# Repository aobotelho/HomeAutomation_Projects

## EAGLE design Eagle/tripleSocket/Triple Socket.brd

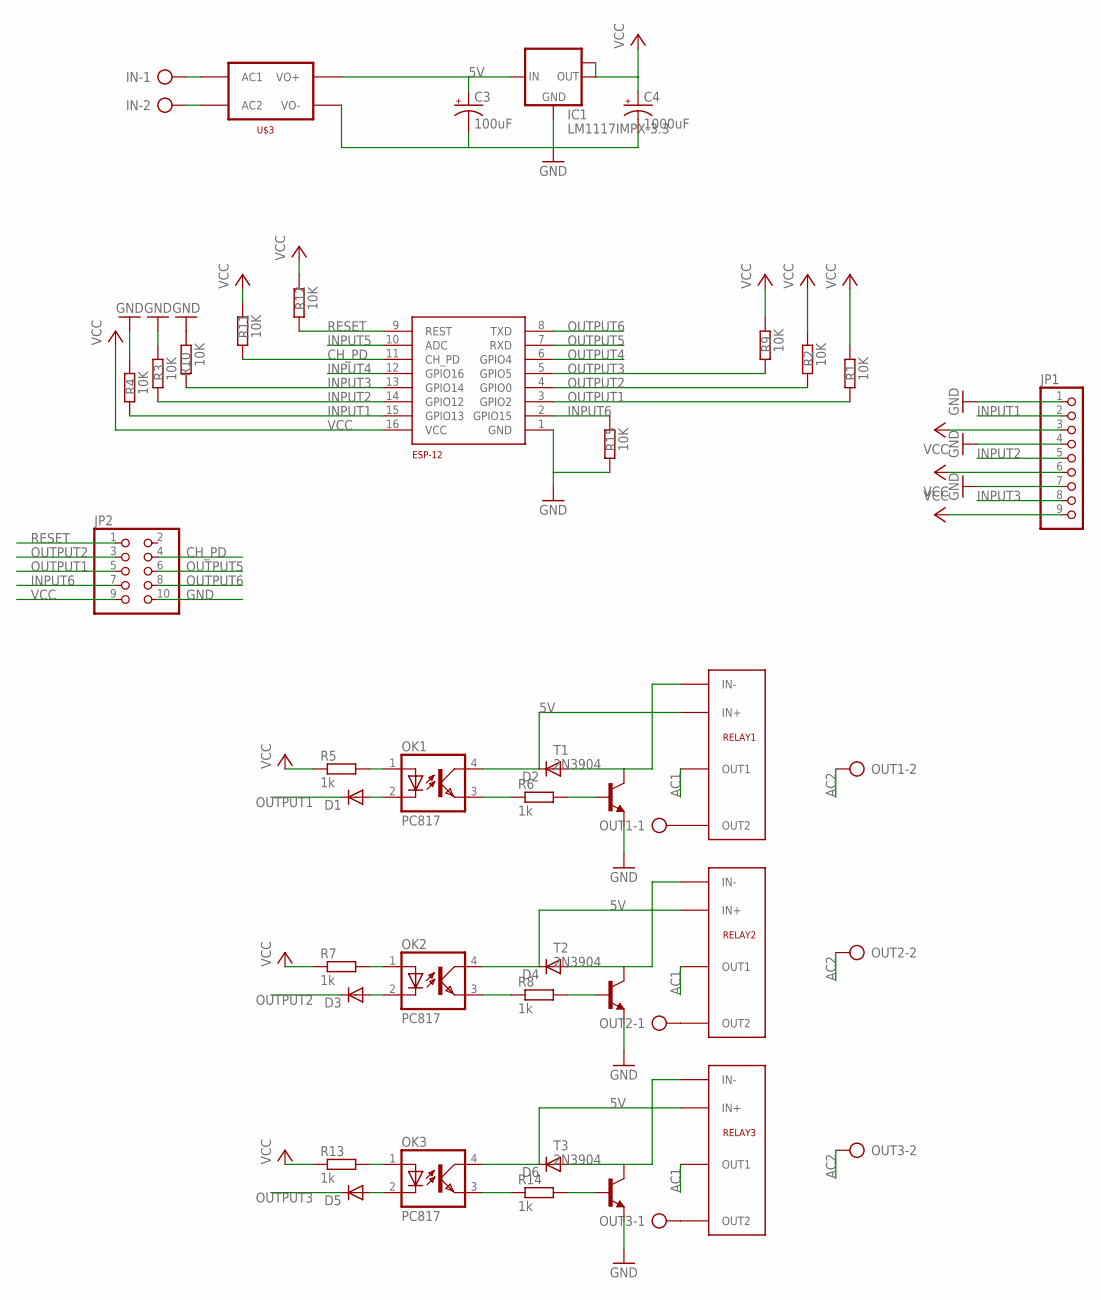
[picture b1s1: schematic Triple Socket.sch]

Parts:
C3: 100uF; E5-10,5
C4: 1000uF; E5-10,5
D1, D2, D3, D4, D5, D6: DIODE-SOD80C; SOD80C
ESP-12: ESP8266_ESP-12; ESP8266-ESP12
IC1: LM1117IMPX-3.3; SOT223
IN: AK500/2-H
JP1: PINHD-1X9; 1X09
JP2: PINHD-2X5; 2X05
OK1, OK2, OK3: PC817; DIL04
OUT1, OUT2, OUT3: AK500/2-H
R1, R2, R3, R4, R9, R10, R11, R12, R15: 10K; R0805
R5, R6, R7, R8, R13, R14: 1k; R0805
RELAY1, RELAY2, RELAY3: G3MB-202P
T1, T2, T3: 2N3904; TO92
U$3: HLK-PM01

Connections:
5V: C3.+, D2.C, D4.C, D6.C, IC1.3 (IN), OK1.4 (COL), OK2.4 (COL), OK3.4 (COL), RELAY1.IN+, RELAY2.IN+, RELAY3.IN+, U$3.VO+
AC1: IN.1, RELAY1.OUT1, RELAY2.OUT1, RELAY3.OUT1, U$3.AC1
AC2: IN.2, OUT1.2, OUT2.2, OUT3.2, U$3.AC2
CH_PD: ESP-12.11 (CH_PD), JP2.4, R11.1
GND: C3.-, C4.-, ESP-12.1 (GND), IC1.1 (GND), JP1.1, JP1.4, JP1.7, JP2.10, R3.1, R4.2, R10.1, R15.1, T1.3 (E), T2.3 (E), T3.3 (E), U$3.VO-
INPUT1: ESP-12.15 (GPIO13), JP1.2, R4.1
INPUT2: ESP-12.14 (GPIO12), JP1.5, R3.2
INPUT3: ESP-12.13 (GPIO14), JP1.8, R10.2
INPUT4: ESP-12.12 (GPIO16)
INPUT5: ESP-12.10 (ADC)
INPUT6: ESP-12.2 (GPIO15), JP2.7, R15.2
unnamed: OUT2.1, RELAY2.OUT2
unnamed: R14.2, T3.2 (B)
unnamed: D6.A, RELAY3.IN-, T3.1 (C)
unnamed: OUT1.1, RELAY1.OUT2
unnamed: OUT3.1, RELAY3.OUT2
unnamed: R6.2, T1.2 (B)
unnamed: D2.A, RELAY1.IN-, T1.1 (C)
unnamed: R8.2, T2.2 (B)
unnamed: D4.A, RELAY2.IN-, T2.1 (C)
OPTO_EMITTER2: OK2.3 (EMIT), R8.1
OPTO_LED+1: OK1.1 (A), R5.2
OPTO_LED+2: OK2.1 (A), R7.2
OPTO_LED+3: OK3.1 (A), R13.2
OPTO_LED-2: D3.A, OK2.2 (C)
OPT_EMITTER1: OK1.3 (EMIT), R6.1
OPT_EMITTER3: OK3.3 (EMIT), R14.1
OPT_LED-1: D1.A, OK1.2 (C)
OPT_LED-3: D5.A, OK3.2 (C)
OUTPUT1: D1.C, ESP-12.3 (GPIO2), JP2.5, R1.1
OUTPUT2: D3.C, ESP-12.4 (GPIO0), JP2.3, R2.1
OUTPUT3: D5.C, ESP-12.5 (GPIO5), R9.1
OUTPUT4: ESP-12.6 (GPIO4)
OUTPUT5: ESP-12.7 (RXD), JP2.6
OUTPUT6: ESP-12.8 (TXD), JP2.8
RESET: ESP-12.9 (REST), JP2.1, R12.1
VCC: C4.+, ESP-12.16 (VCC), IC1.2 (OUT), IC1.TAB (OUT1), JP1.3, JP1.6, JP1.9, JP2.9, R1.2, R2.2, R5.1, R7.1, R9.2, R11.2, R12.2, R13.1

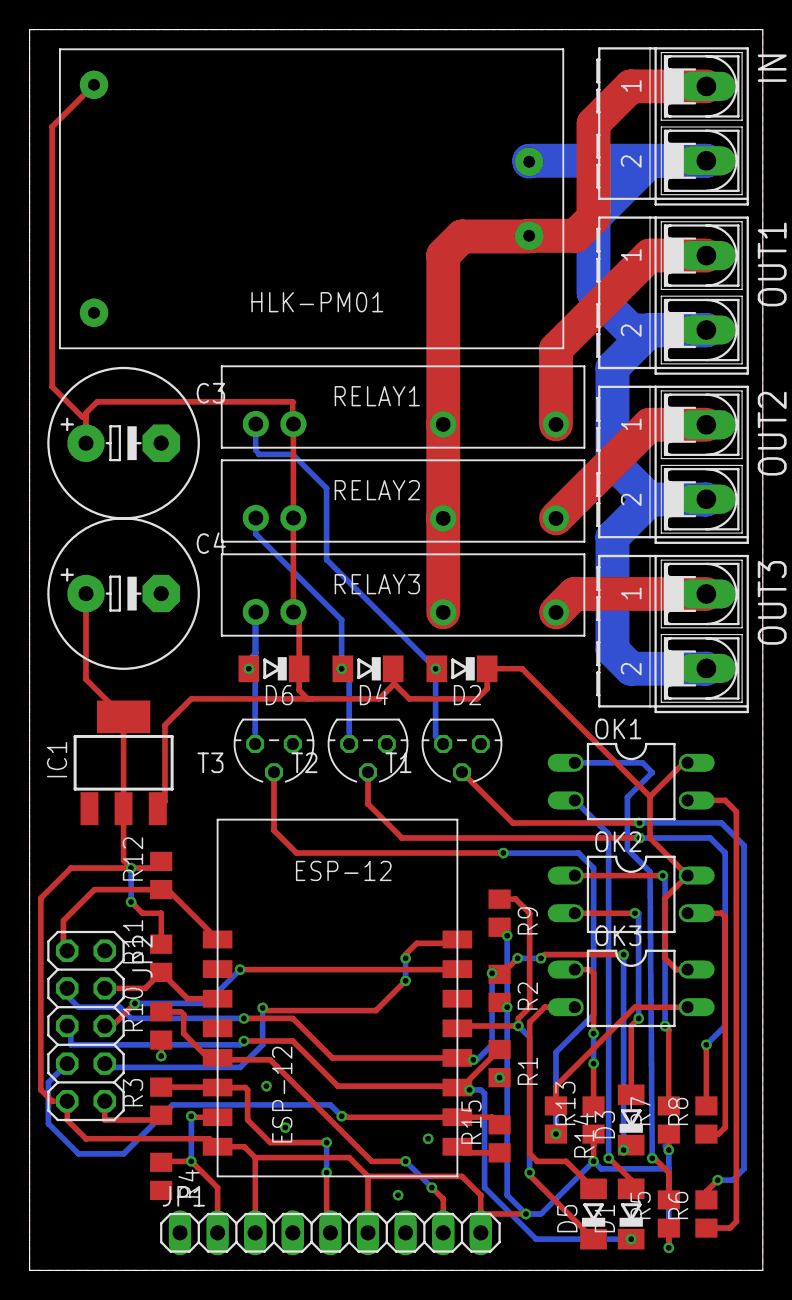
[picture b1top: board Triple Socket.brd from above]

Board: 2 copper layers, 49.5 x 83.8 mm, 41 parts (0 on the bottom side), 34 nets.

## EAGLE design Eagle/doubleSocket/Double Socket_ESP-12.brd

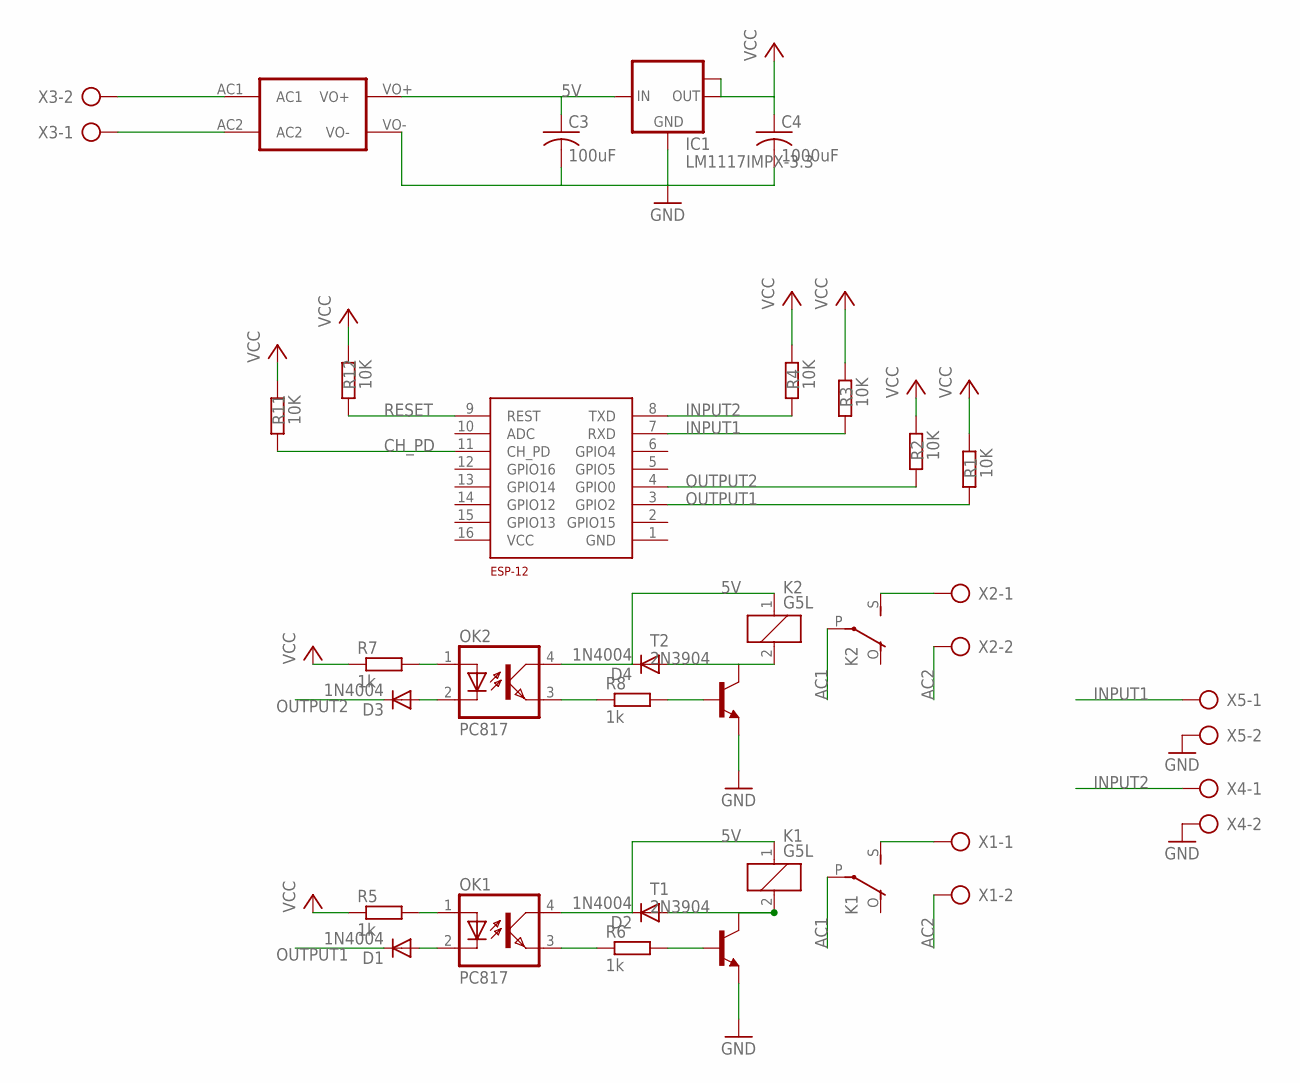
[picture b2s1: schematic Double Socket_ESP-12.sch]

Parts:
C3: 100uF; C0805
C4: 1000uF; C0805
D1, D2, D3, D4: 1N4004; DO41-10
ESP-12: ESP8266_ESP-12; ESP8266-ESP12
IC1: LM1117IMPX-3.3; SOT223
K1, K2: G5L; G5LE
OK1, OK2: PC817; DIL04
R1, R2, R3, R4, R11, R12: 10K; M0805
R5, R6, R7, R8: 1k; M0805
T1, T2: 2N3904; TO92
U$1: HLK-PM01
X1, X2, X3, X4, X5: AK500/2-H

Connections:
5V: C3.1, D2.C, D4.C, IC1.3 (IN), K1.1, K2.1, OK1.4 (COL), OK2.4 (COL), U$1.VO+
AC1: K1.P, K2.P, U$1.AC1, X3.2
AC2: U$1.AC2, X1.2, X2.2, X3.1
CH_PD: ESP-12.11 (CH_PD), R11.1
GND: C3.2, C4.2, IC1.1 (GND), T1.3 (E), T2.3 (E), U$1.VO-, X4.2, X5.2
INPUT1: ESP-12.7 (RXD), R3.2, X5.1
INPUT2: ESP-12.8 (TXD), R4.1, X4.1
unnamed: K1.S, X1.1
unnamed: R6.2, T1.2 (B)
unnamed: D2.A, K1.2, T1.1 (C)
unnamed: R8.2, T2.2 (B)
unnamed: D4.A, K2.2, T2.1 (C)
unnamed: K2.S, X2.1
OPTO_EMITTER1: OK2.3 (EMIT), R8.1
OPTO_LED+1: OK2.1 (A), R7.2
OPTO_LED+2: OK1.1 (A), R5.2
OPTO_LED-1: D3.A, OK2.2 (C)
OPT_EMITTER2: OK1.3 (EMIT), R6.1
OPT_LED-2: D1.A, OK1.2 (C)
OUTPUT1: D1.C, ESP-12.3 (GPIO2), R1.1
OUTPUT2: D3.C, ESP-12.4 (GPIO0), R2.1
RESET: ESP-12.9 (REST), R12.1
VCC: C4.1, IC1.2 (OUT), IC1.TAB (OUT1), R1.2, R2.2, R3.1, R4.2, R5.1, R7.1, R11.2, R12.2

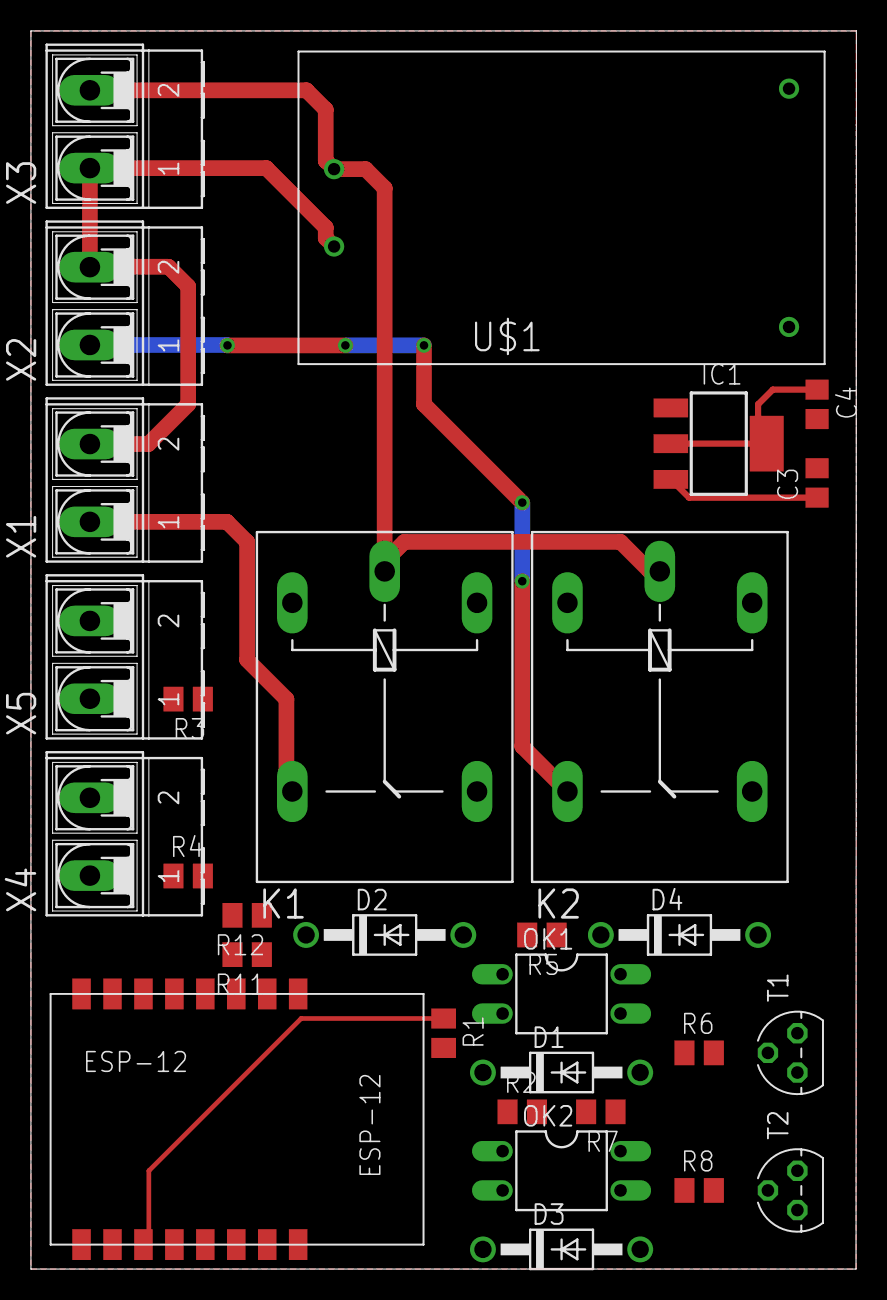
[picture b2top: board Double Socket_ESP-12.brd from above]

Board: 2 copper layers, 53.3 x 80.0 mm, 30 parts (0 on the bottom side), 23 nets.

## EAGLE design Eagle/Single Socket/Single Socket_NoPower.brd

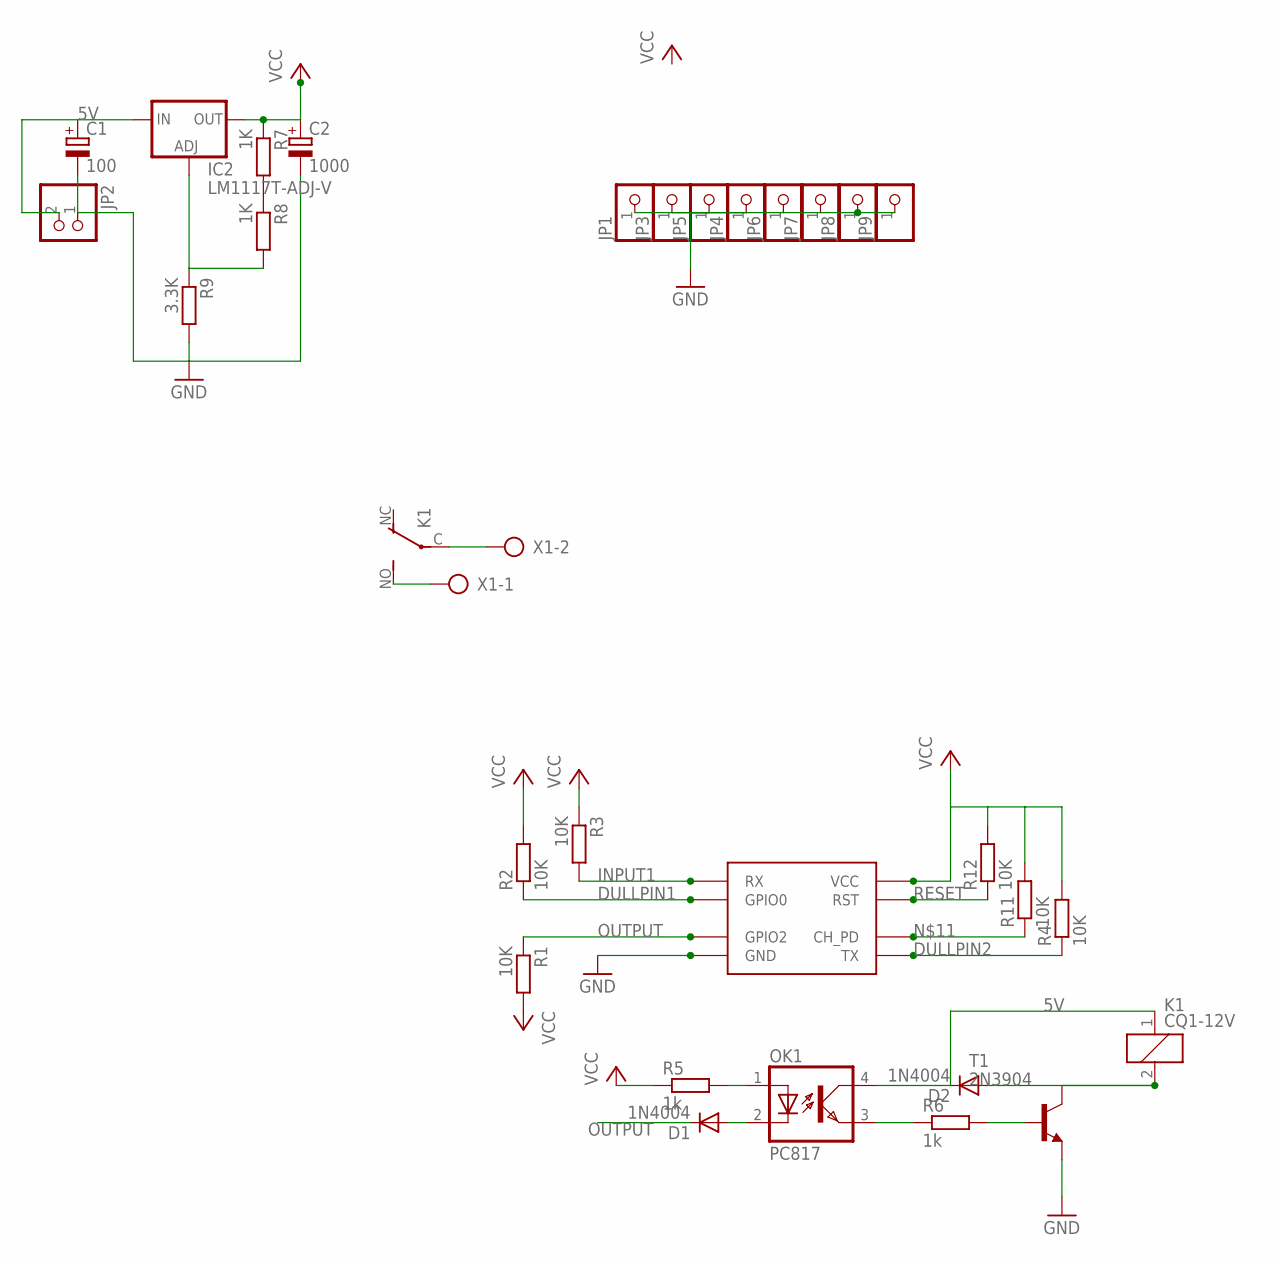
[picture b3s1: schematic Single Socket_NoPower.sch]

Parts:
C1: 100; E5-10,5
C2: 1000; E5-10,5
D1, D2: 1N4004; DO41-10
IC2: LM1117T-ADJ-V; TO220V
JP1, JP3, JP4, JP5, JP6, JP7, JP8, JP9: PINHD-1X1; 1X01
JP2: PINHD-1X2; 1X02
K1: CQ1-12V; CQ1
OK1: PC817; DIL04
R1, R2, R3, R4, R11, R12: 10K; 0207/10
R5, R6: 1k; 0207/10
R7, R8: 1K; 0207/10
R9: 3.3K; 0207/10
T1: 2N3904; TO92
U$2: ESP8266
X1: AK500/2-H

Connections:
5V: C1.+, D2.C, IC2.3 (IN), JP2.2, K1.1, OK1.4 (COL)
DULLPIN1: R2.1, U$2.GPIO0
DULLPIN2: R4.1, U$2.TX
GND: C1.-, C2.-, JP1.1, JP2.1, JP3.1, JP4.1, JP5.1, JP6.1, JP7.1, JP8.1, JP9.1, R9.2, T1.3 (E), U$2.GND
INPUT1: R3.2, U$2.RX
unnamed: K1.C, X1.2
unnamed: K1.NO (S), X1.1
unnamed: OK1.1 (A), R5.2
unnamed: OK1.3 (EMIT), R6.1
unnamed: D1.A, OK1.2 (C)
unnamed: R6.2, T1.2 (B)
unnamed: D2.A, K1.2, T1.1 (C)
unnamed: R11.1, U$2.CH_PD
unnamed: R7.2, R8.1
unnamed: IC2.1 (ADJ), R8.2, R9.1
OUTPUT: D1.C, R1.1, U$2.GPIO2
RESET: R12.1, U$2.RST
VCC: C2.+, IC2.2 (OUT), R1.2, R2.2, R3.1, R4.2, R5.1, R7.1, R11.2, R12.2, U$2.VCC

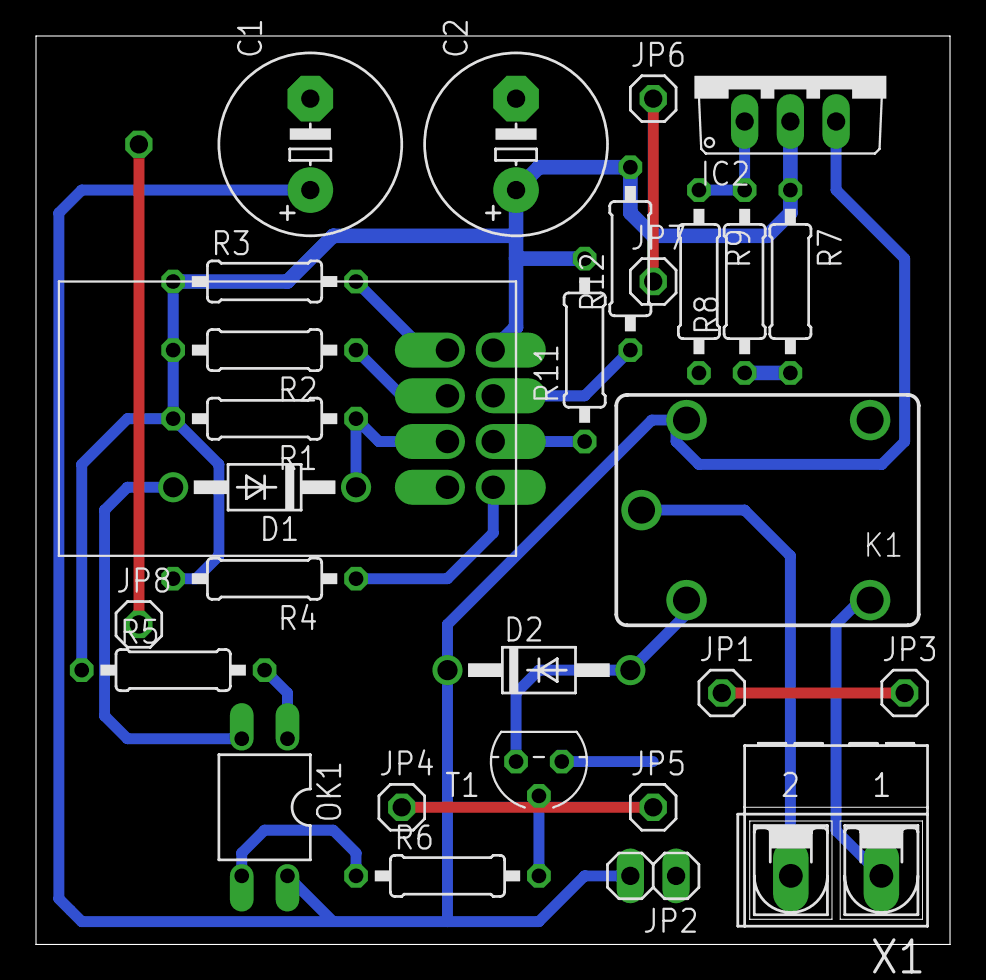
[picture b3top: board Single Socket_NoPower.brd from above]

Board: 2 copper layers, 50.8 x 50.5 mm, 30 parts (1 on the bottom side), 18 nets.

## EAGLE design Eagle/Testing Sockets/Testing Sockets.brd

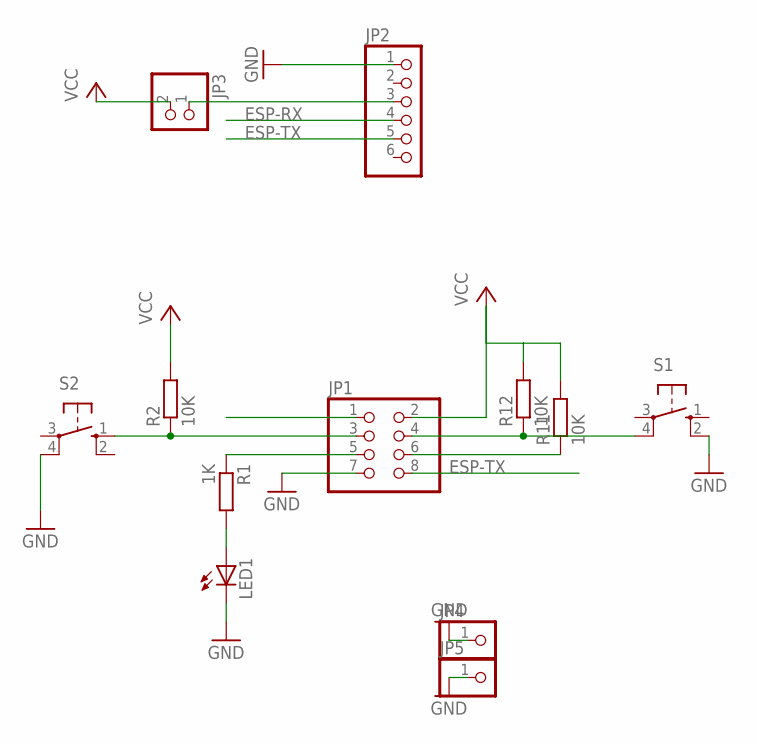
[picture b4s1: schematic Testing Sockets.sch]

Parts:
JP1: PINHD-2X4; 2X04
JP2: PINHD-1X6; 1X06
JP3: PINHD-1X2; 1X02
JP4, JP5: PINHD-1X1; 1X01
LED1: LED5MM
R1: 1K; 0207/10
R2, R11, R12: 10K; 0207/10
S1: 10-XX; B3F-10XX
S2: 10-XX; B3F-10XX; MPN B3F-1000

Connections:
ESP-RX: JP1.1, JP2.4
ESP-TX: JP1.8, JP2.5
GND: JP1.7, JP2.1, JP4.1, JP5.1, LED1.K (C), S1.2 (S1), S2.4 (P1)
unnamed: JP1.5, R1.1
unnamed: LED1.A, R1.2
unnamed: JP2.3, JP3.1
unnamed: JP1.6, R11.1
unnamed: JP1.4, R12.1, S1.4 (P1)
SOCKET1: JP1.3, R2.1, S2.1 (S)
VCC: JP1.2, JP3.2, R2.2, R11.2, R12.2

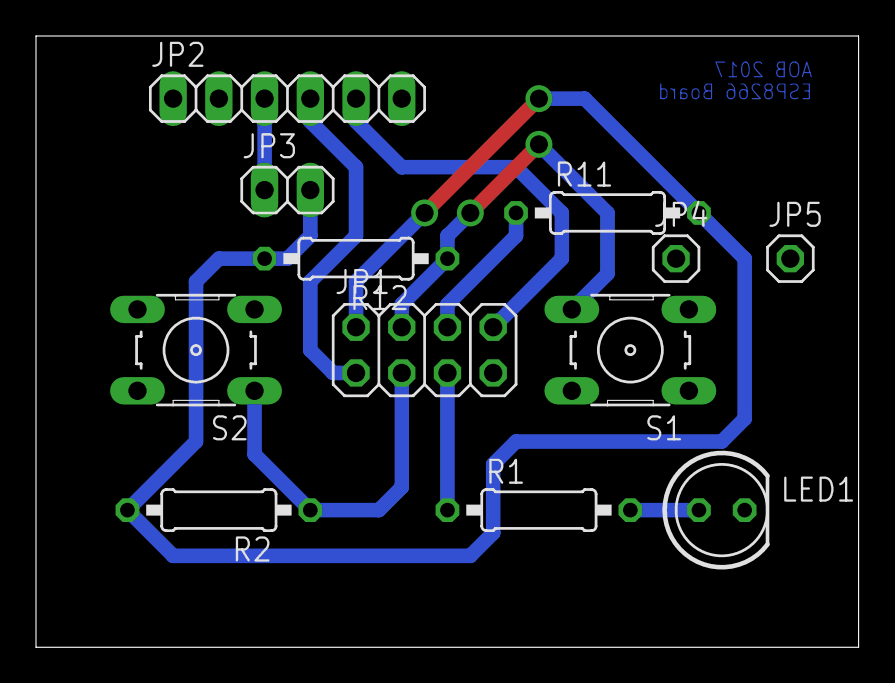
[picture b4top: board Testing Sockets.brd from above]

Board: 2 copper layers, 45.7 x 34.0 mm, 12 parts (0 on the bottom side), 10 nets.

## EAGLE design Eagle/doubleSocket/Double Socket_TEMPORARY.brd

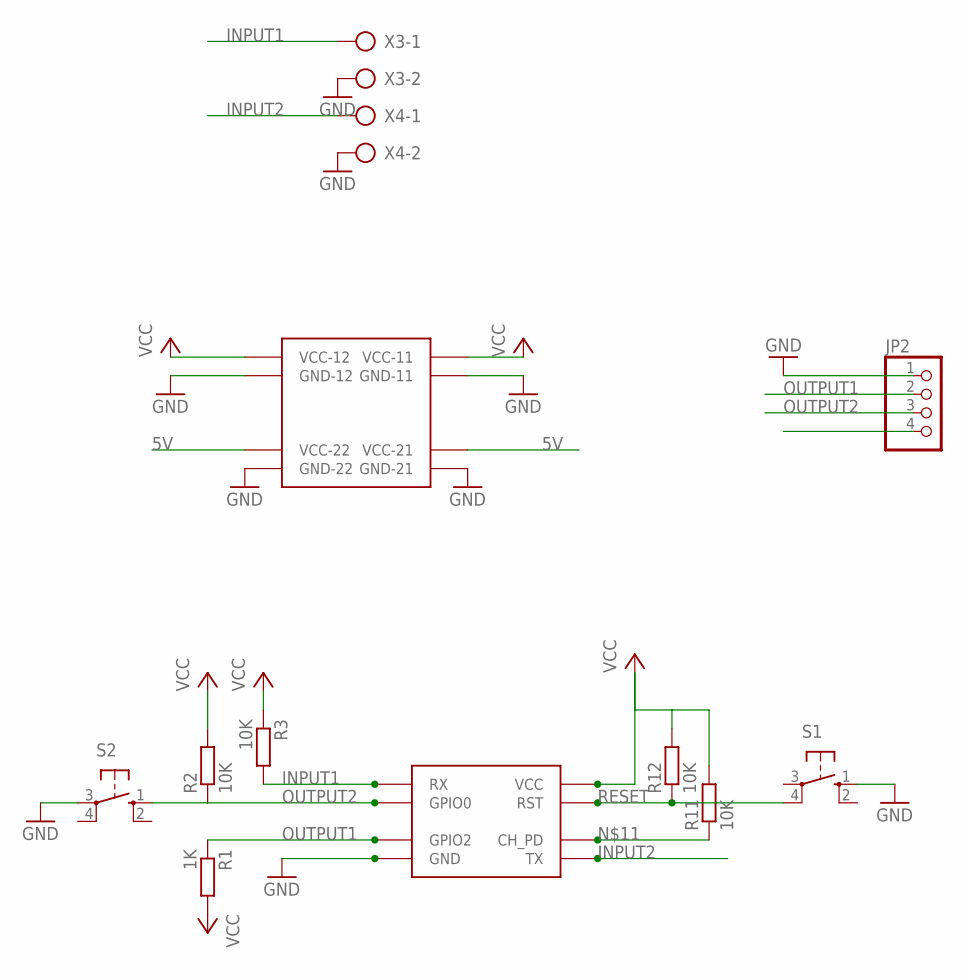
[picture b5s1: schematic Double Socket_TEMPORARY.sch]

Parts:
JP2: PINHD-1X4; 1X04
R1: 1K; 0207/10
R2, R3, R11, R12: 10K; 0207/10
S1, S2: 40-XX; B3F-40XX; MPN B3F-4000
U$1: YWROBOT
U$2: ESP8266
X3, X4: AK500/2-H

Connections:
5V: JP2.4, U$1.VCC-21, U$1.VCC-22
GND: JP2.1, S1.1 (S), S2.3, U$1.GND-11, U$1.GND-12, U$1.GND-21, U$1.GND-22, U$2.GND, X3.2, X4.2
INPUT1: R3.2, U$2.RX, X3.1
INPUT2: U$2.TX, X4.1
unnamed: R11.1, U$2.CH_PD
OUTPUT1: JP2.2, R1.1, U$2.GPIO2
OUTPUT2: JP2.3, R2.1, S2.1 (S), U$2.GPIO0
RESET: R12.1, S1.4 (P1), U$2.RST
VCC: R1.2, R2.2, R3.1, R11.2, R12.2, U$1.VCC-11, U$1.VCC-12, U$2.VCC

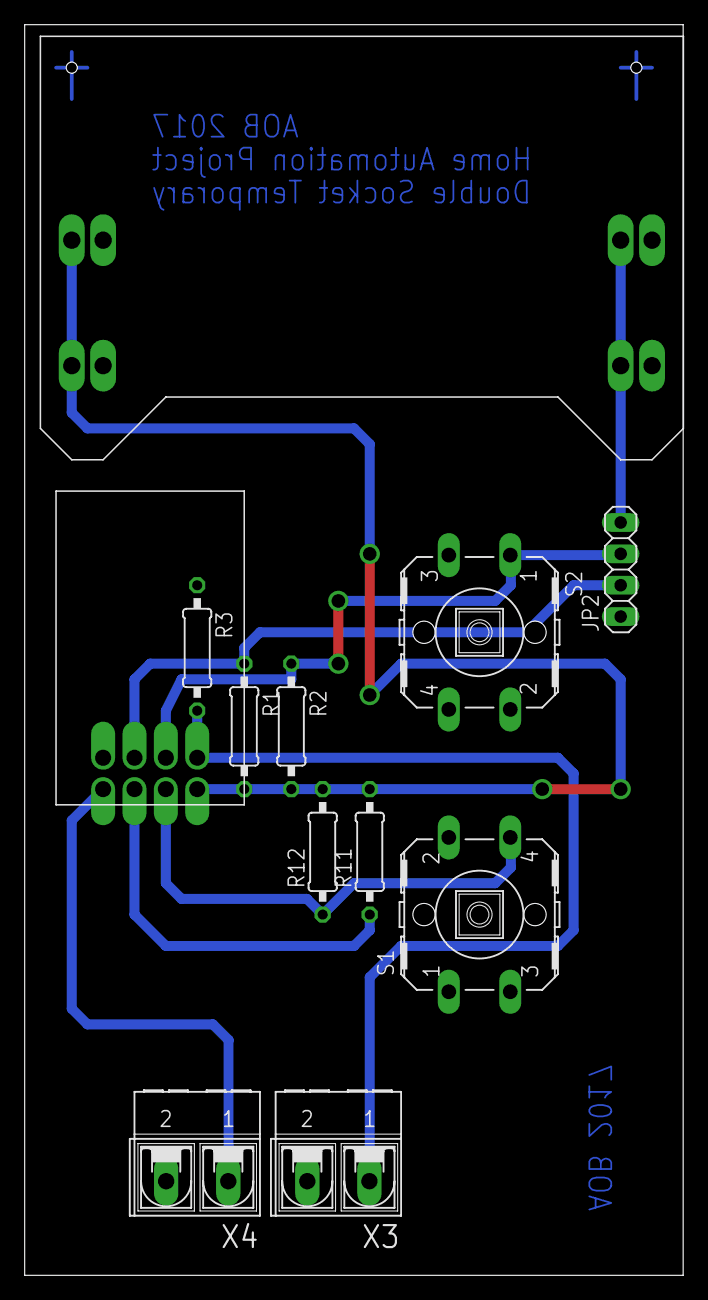
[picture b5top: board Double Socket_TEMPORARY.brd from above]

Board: 2 copper layers, 53.3 x 101.3 mm, 12 parts (0 on the bottom side), 9 nets.

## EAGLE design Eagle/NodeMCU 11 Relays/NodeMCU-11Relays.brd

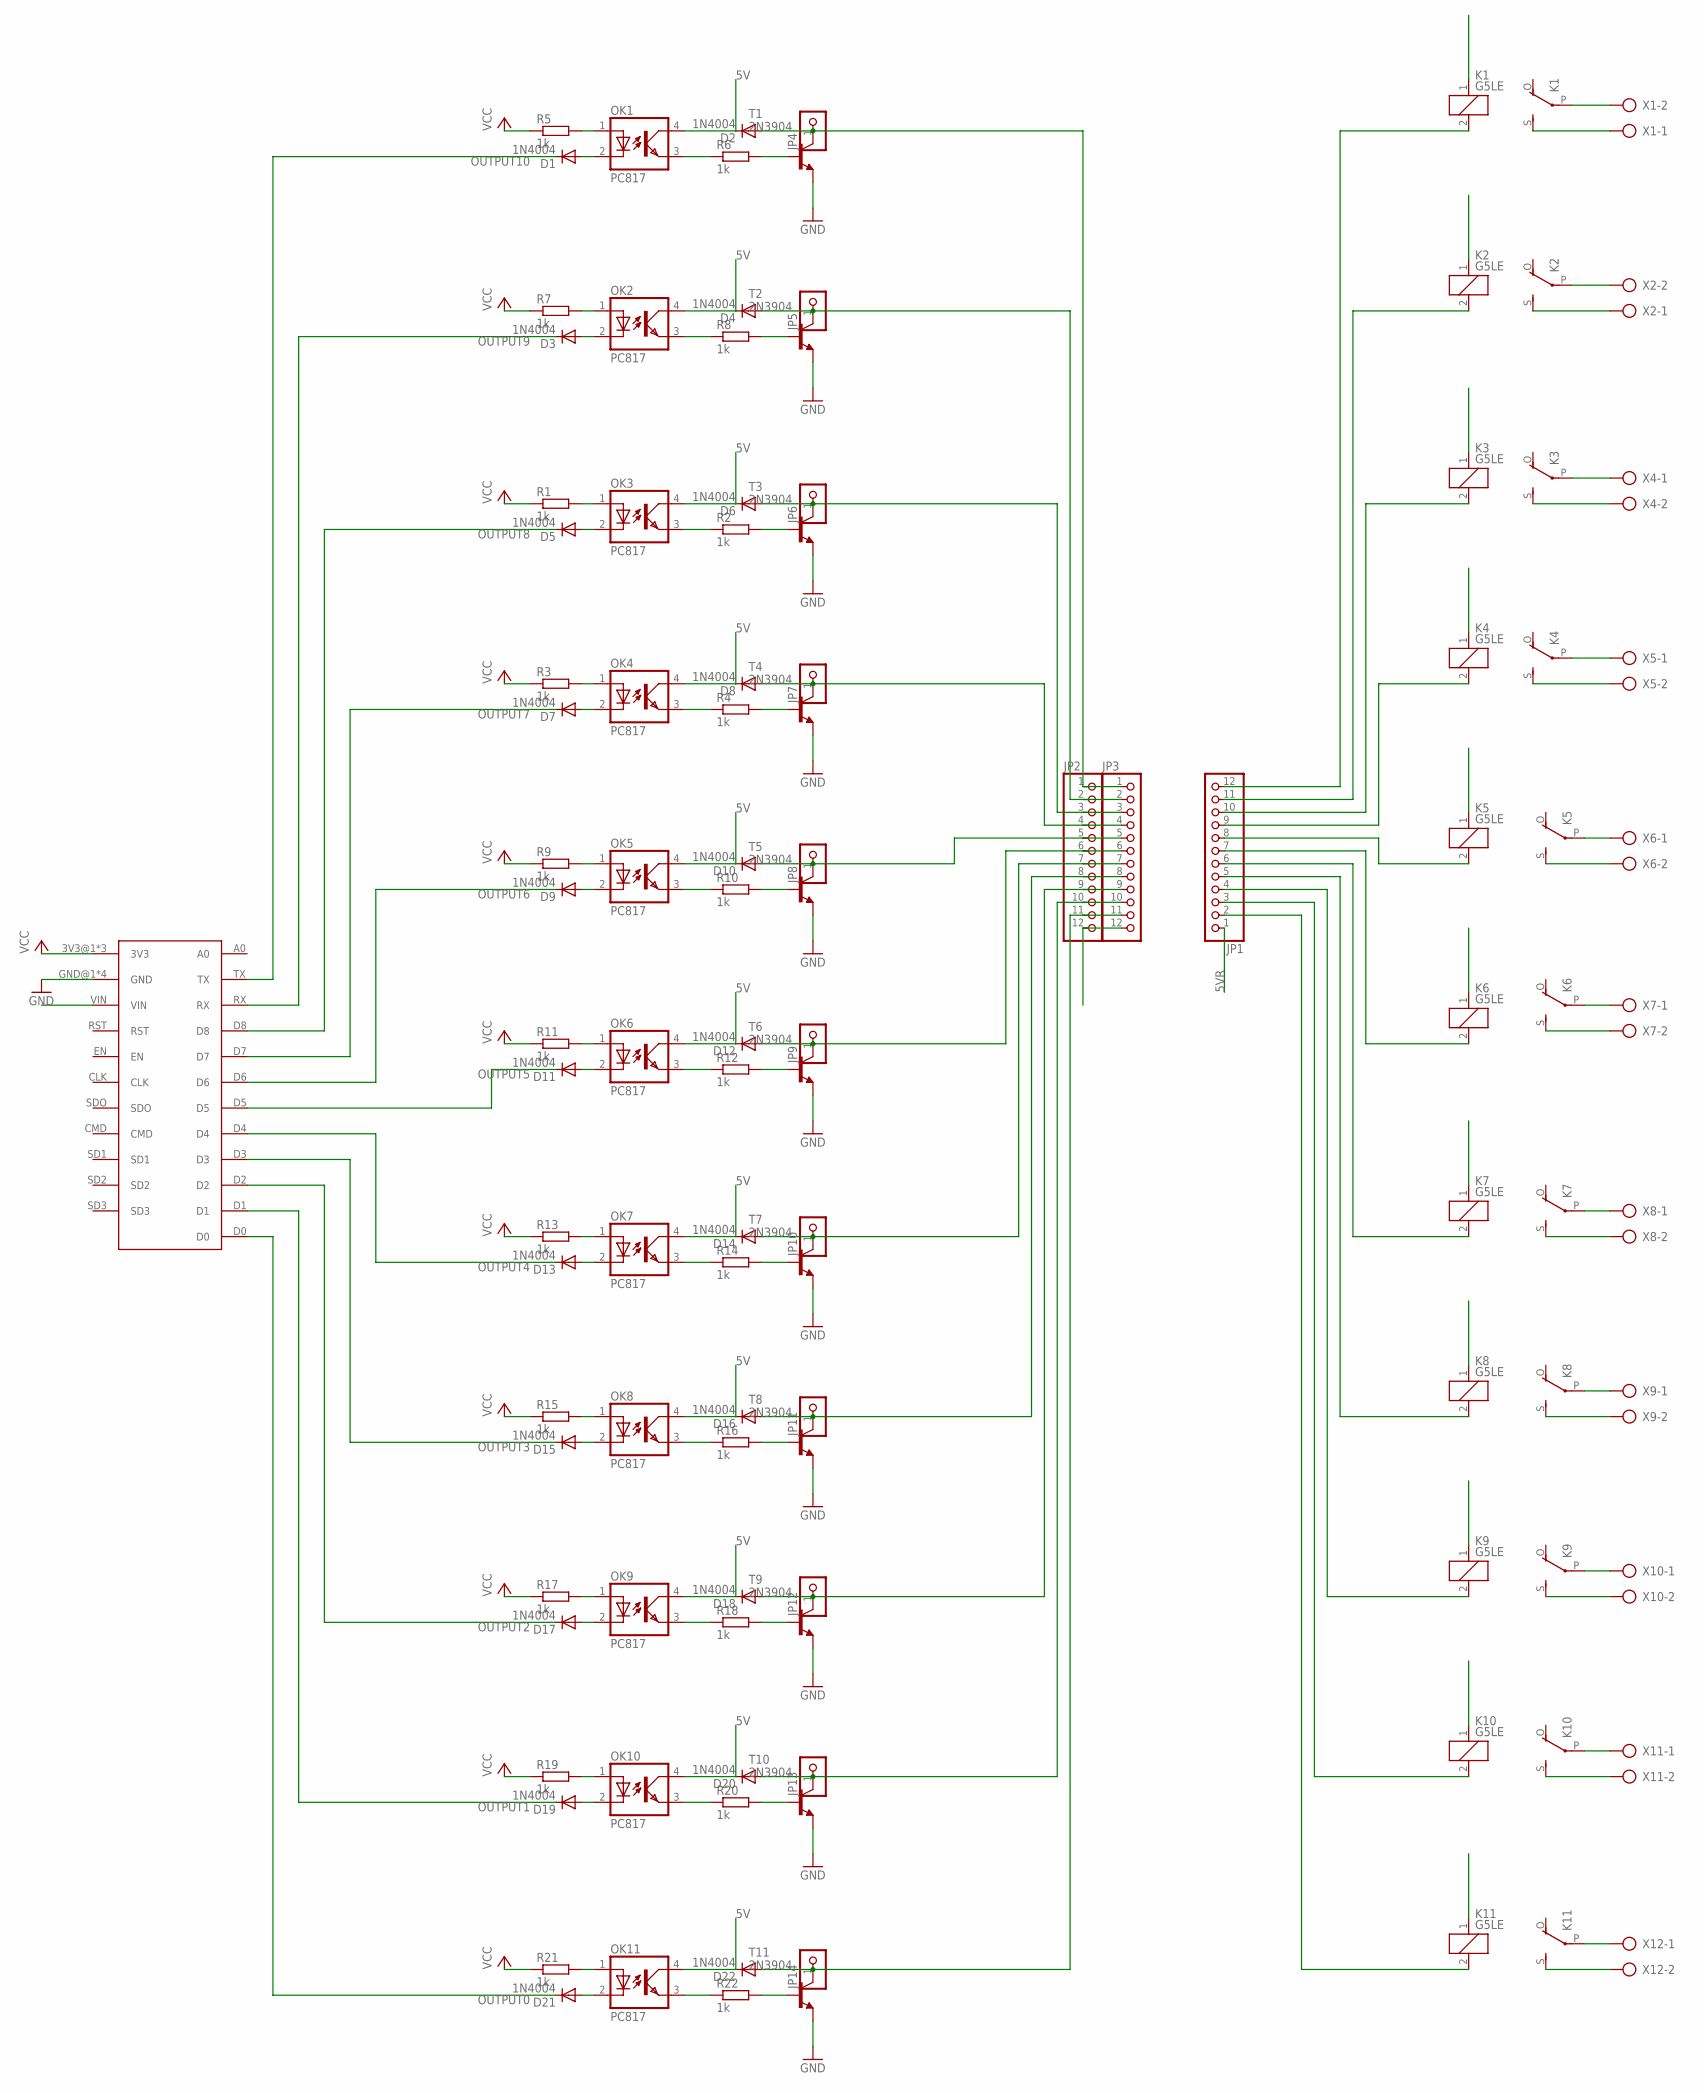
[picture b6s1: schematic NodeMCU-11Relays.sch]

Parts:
D1, D2, D3, D4, D5, D6, D7, D8, D9, D10, D11, D12, D13, D14, D15, D16, D17, D18, D19, D20, D21, D22: 1N4004; DO41-10
JP1, JP2, JP3: PINHD-1X12; 1X12
JP4, JP5, JP6, JP7, JP8, JP9, JP10, JP11, JP12, JP13, JP14: PINHD-1X1; 1X01
K1, K2, K3, K4, K5, K6, K7, K8, K9, K10, K11: G5LE
OK1, OK2, OK3, OK4, OK5, OK6, OK7, OK8, OK9, OK10, OK11: PC817; DIL04
R1, R2, R3, R4, R5, R6, R7, R8, R9, R10, R11, R12, R13, R14, R15, R16, R17, R18, R19, R20, R21, R22: 1k; 0207/10
T1, T2, T3, T4, T5, T6, T7, T8, T9, T10, T11: 2N3904; TO92
U$1: NODEMCU-1.0
X1, X2, X4, X5, X6, X7, X8, X9, X10, X11, X12: AK500/2-H

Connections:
5V: D2.C, D4.C, D6.C, D8.C, D10.C, D12.C, D14.C, D16.C, D18.C, D20.C, D22.C, JP2.12, JP3.12, OK1.4 (COL), OK2.4 (COL), OK3.4 (COL), OK4.4 (COL), OK5.4 (COL), OK6.4 (COL), OK7.4 (COL), OK8.4 (COL), OK9.4 (COL), OK10.4 (COL), OK11.4 (COL), U$1.VIN
5VR: JP1.1, K1.1, K2.1, K3.1, K4.1, K5.1, K6.1, K7.1, K8.1, K9.1, K11.1
GND: T1.3 (E), T2.3 (E), T3.3 (E), T4.3 (E), T5.3 (E), T6.3 (E), T7.3 (E), T8.3 (E), T9.3 (E), T10.3 (E), T11.3 (E), U$1.GND@1 (GND), U$1.GND@2 (GND), U$1.GND@3 (GND), U$1.GND@4 (GND)
unnamed: K1.P, X1.2
unnamed: K1.S, X1.1
unnamed: OK1.1 (A), R5.2
unnamed: OK1.3 (EMIT), R6.1
unnamed: D1.A, OK1.2 (C)
unnamed: OK2.1 (A), R7.2
unnamed: R6.2, T1.2 (B)
unnamed: D2.A, JP2.1, JP3.1, JP4.1, T1.1 (C)
unnamed: OK2.3 (EMIT), R8.1
unnamed: D3.A, OK2.2 (C)
unnamed: OK3.1 (A), R1.2
unnamed: R8.2, T2.2 (B)
unnamed: D4.A, JP2.2, JP3.2, JP5.1, T2.1 (C)
unnamed: K2.S, X2.1
unnamed: K2.P, X2.2
unnamed: OK3.3 (EMIT), R2.1
unnamed: D5.A, OK3.2 (C)
unnamed: R2.2, T3.2 (B)
unnamed: D6.A, JP2.3, JP3.3, JP6.1, T3.1 (C)
unnamed: OK4.1 (A), R3.2
unnamed: OK4.3 (EMIT), R4.1
unnamed: D7.A, OK4.2 (C)
unnamed: R4.2, T4.2 (B)
unnamed: D8.A, JP2.4, JP3.4, JP7.1, T4.1 (C)
unnamed: OK5.1 (A), R9.2
unnamed: OK5.3 (EMIT), R10.1
unnamed: D9.A, OK5.2 (C)
unnamed: R10.2, T5.2 (B)
unnamed: D10.A, JP2.5, JP3.5, JP8.1, T5.1 (C)
unnamed: OK6.1 (A), R11.2
unnamed: OK6.3 (EMIT), R12.1
unnamed: D11.A, OK6.2 (C)
unnamed: R12.2, T6.2 (B)
unnamed: D12.A, JP2.6, JP3.6, JP9.1, T6.1 (C)
unnamed: OK7.1 (A), R13.2
unnamed: OK7.3 (EMIT), R14.1
unnamed: D13.A, OK7.2 (C)
unnamed: R14.2, T7.2 (B)
unnamed: D14.A, JP2.7, JP3.7, JP10.1, T7.1 (C)
unnamed: OK8.1 (A), R15.2
unnamed: OK8.3 (EMIT), R16.1
unnamed: D15.A, OK8.2 (C)
unnamed: R16.2, T8.2 (B)
unnamed: D16.A, JP2.8, JP3.8, JP11.1, T8.1 (C)
unnamed: OK9.1 (A), R17.2
unnamed: OK9.3 (EMIT), R18.1
unnamed: D17.A, OK9.2 (C)
unnamed: R18.2, T9.2 (B)
unnamed: D18.A, JP2.9, JP3.9, JP12.1, T9.1 (C)
unnamed: OK10.1 (A), R19.2
unnamed: OK10.3 (EMIT), R20.1
unnamed: D19.A, OK10.2 (C)
unnamed: R20.2, T10.2 (B)
unnamed: D20.A, JP2.10, JP3.10, JP13.1, T10.1 (C)
unnamed: OK11.1 (A), R21.2
unnamed: OK11.3 (EMIT), R22.1
unnamed: D21.A, OK11.2 (C)
unnamed: R22.2, T11.2 (B)
unnamed: D22.A, JP2.11, JP3.11, JP14.1, T11.1 (C)
unnamed: K3.P, X4.1
unnamed: K4.P, X5.1
unnamed: K5.P, X6.1
unnamed: K6.P, X7.1
unnamed: K7.P, X8.1
unnamed: K8.P, X9.1
unnamed: K9.P, X10.1
unnamed: K10.P, X11.1
unnamed: K11.P, X12.1
unnamed: K3.S, X4.2
unnamed: K4.S, X5.2
unnamed: K5.S, X6.2
unnamed: K6.S, X7.2
unnamed: K7.S, X8.2
unnamed: K8.S, X9.2
unnamed: K9.S, X10.2
unnamed: K10.S, X11.2
unnamed: K11.S, X12.2
unnamed: JP1.2, K11.2
unnamed: JP1.3, K10.2
unnamed: JP1.4, K9.2
unnamed: JP1.5, K8.2
unnamed: JP1.6, K7.2
unnamed: JP1.7, K6.2
unnamed: JP1.8, K5.2
unnamed: JP1.9, K4.2
unnamed: JP1.10, K3.2
unnamed: JP1.11, K2.2
unnamed: JP1.12, K1.2
OUTPUT0: D21.C, U$1.D0
OUTPUT1: D19.C, U$1.D1
OUTPUT2: D17.C, U$1.D2
OUTPUT3: D15.C, U$1.D3
OUTPUT4: D13.C, U$1.D4
OUTPUT5: D11.C, U$1.D5
OUTPUT6: D9.C, U$1.D6
OUTPUT7: D7.C, U$1.D7
OUTPUT8: D5.C, U$1.D8
OUTPUT9: D3.C, U$1.RX
OUTPUT10: D1.C, U$1.TX
VCC: R1.1, R3.1, R5.1, R7.1, R9.1, R11.1, R13.1, R15.1, R17.1, R19.1, R21.1, U$1.3V3@1 (3V3), U$1.3V3@2 (3V3), U$1.3V3@3 (3V3)

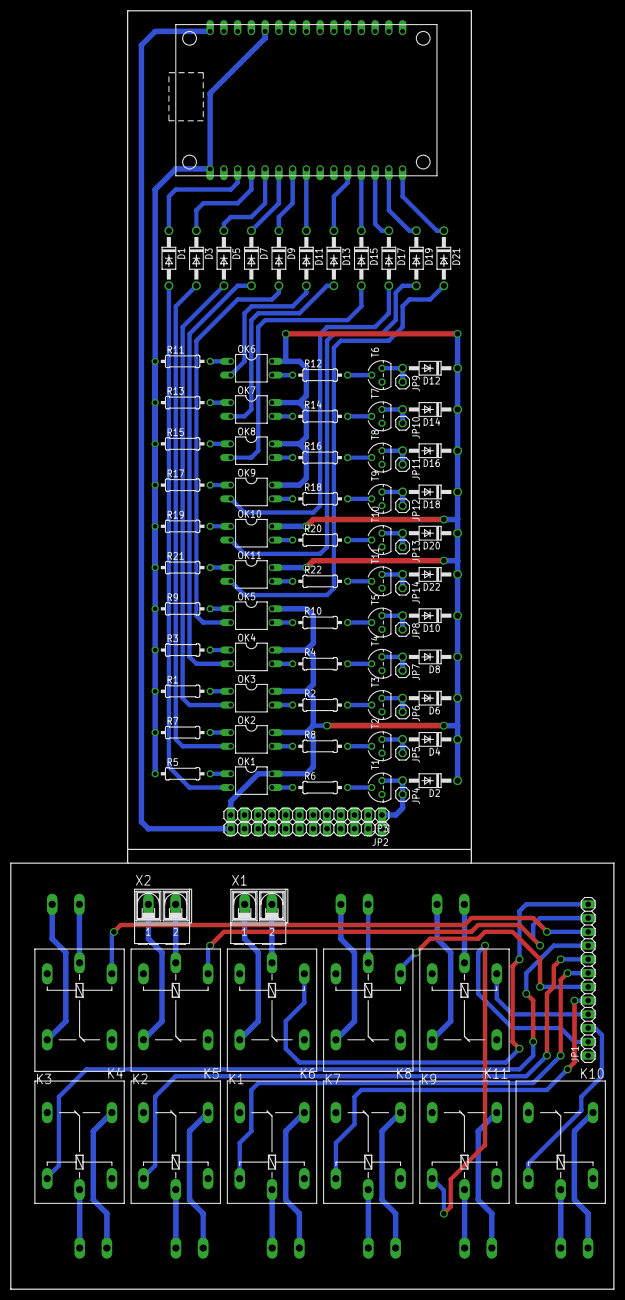
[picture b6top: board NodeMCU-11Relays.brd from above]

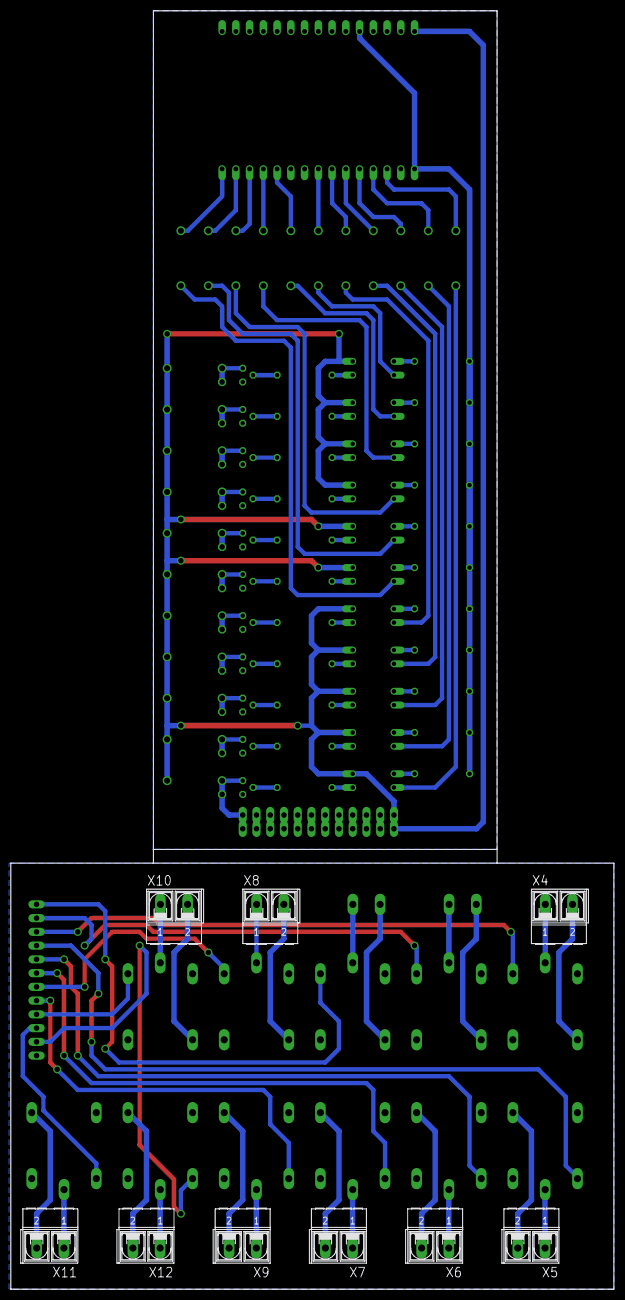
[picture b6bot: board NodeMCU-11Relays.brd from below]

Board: 2 copper layers, 111.4 x 236.2 mm, 103 parts (9 on the bottom side), 103 nets.

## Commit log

2017-02-16 testing sockets project
2017-05-23 Created HASS_FOlder and uploaded the original files
2017-05-23 Updated gitignore
2017-06-05 Added first set of Eagle files
2017-06-05 Changed arduino files to arduino folder
2017-10-03 First version of ESP-12
2017-10-03 Version with ESP-01 breakout
2017-10-03 Added ESP-12 library
2017-10-24 temp version
2017-10-24 Updated gitignore to ignore eagle temp files
2017-10-24 Create LICENSE
2017-10-25 Added oi.txt
2020-06-14 Working version of automatic door!! Lacking documentation
2020-10-17 First Working version
2020-10-17 Added Temperature Controller
2020-10-17 Updated gitnignore
2020-10-20 New Version with average of 5 last measurements
2020-12-06 Version with DS18B20
2022-01-02 Trying to fix large file update
2022-01-03 First commit UI
2022-01-04 Added images
2022-01-09 First version in dev
2022-01-09 Removed MPU6050
2022-01-09 First version of UI
2022-01-09 Flexible font size for texts
2022-01-09 Forgot one flexible font in the last commit
2022-01-09 First test integrated
2022-01-09 Fixed path for images on raspberry pi
2022-01-09 Trying to add target temp controller
2022-01-09 still in the fight
2022-01-09 Still trying
2022-01-09 Error on initial messages
2022-01-09 Working target temp
2022-01-09 added red timeout
2022-01-09 Fixed round to write new target temp
2022-01-09 Added initial target temp
2022-09-08 Fixed target temp error
2022-09-08 Fixed error on init
